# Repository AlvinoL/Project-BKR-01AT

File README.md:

# Project-BKR-01AT
Prova final de circuitos impressos

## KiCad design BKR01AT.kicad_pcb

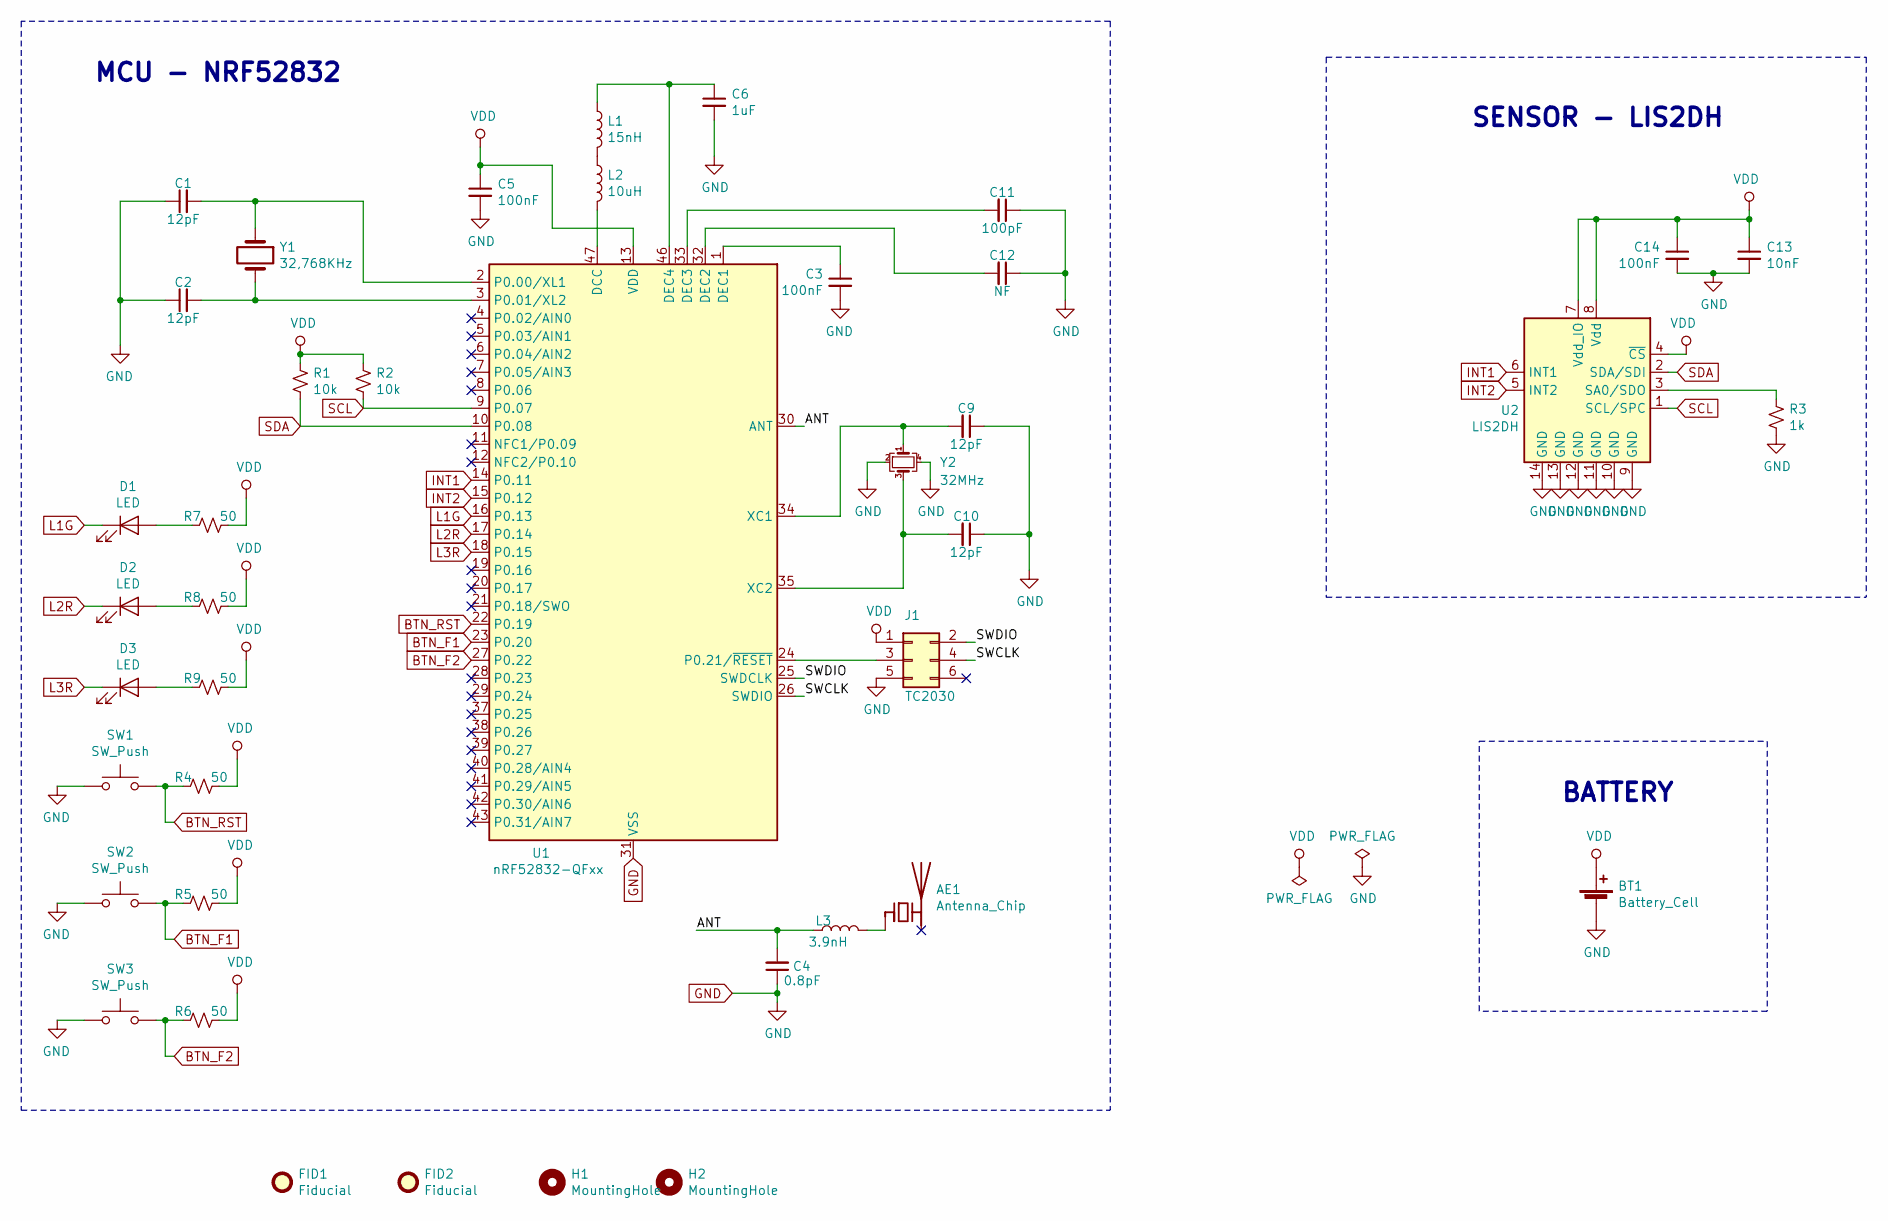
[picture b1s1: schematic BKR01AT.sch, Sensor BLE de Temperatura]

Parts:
AE1: Antenna_Chip; 2450AT18B100
BT1: Battery_Cell; Battery_Panasonic_CR2032-VS1N_Vertical_CircularHoles
C1, C2, C9, C10: 12pF; C_0402_1005Metric
C3, C5, C14: 100nF; C_0402_1005Metric
C4: 0.8pF; C_0402_1005Metric
C6: 1uF; C_0402_1005Metric
C11: 100pF; C_0402_1005Metric
C12: NF; C_0402_1005Metric
C13: 10nF; C_0402_1005Metric
D1, D2, D3: LED; LED_0402_1005Metric
FID1, FID2: Fiducial; Fiducial_0.5mm_Mask1.5mm
H1, H2: MountingHole; MountingHole_2mm
J1: TC2030; Tag-Connect_TC2030-IDC-NL_2x03_P1.27mm_Vertical
L1: 15nH; L_0402_1005Metric
L2: 10uH; L_0805_2012Metric
L3: 3.9nH; L_0402_1005Metric
R1, R2: 10k; R_0402_1005Metric
R3: 1k; R_0402_1005Metric
R4, R5, R6, R7, R8, R9: 50; R_0402_1005Metric
SW1, SW2, SW3: SW_Push; SW_Push_1P1T_NO_6x6mm_H9.5mm
U1: nRF52832-QFxx; QFN-48-1EP_6x6mm_P0.4mm_EP4.6x4.6mm
U2: LIS2DH; LGA-14_2x2mm_P0.35mm_LayoutBorder3x4y
Y1: 32,768KHz; Crystal_SMD_3215-2Pin_3.2x1.5mm
Y2: 32MHz; Crystal_SMD_2016-4Pin_2.0x1.6mm

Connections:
/ANT: C4.2, L3.1, U1.30 (ANT)
/SWCLK: J1.4, U1.26 (SWDIO)
/SWDIO: J1.2, U1.25 (SWDCLK)
BTN_F1: R5.2, SW2.2, U1.23 (P0.20)
BTN_F2: R6.2, SW3.2, U1.27 (P0.22)
BTN_RST: R4.2, SW1.2, U1.22 (P0.19)
GND: BT1.2 (-), C1.1, C2.1, C3.2, C4.1, C5.2, C6.2, C9.1, C10.1, C11.1, C12.1, C13.2, C14.2, J1.5, R3.2, SW1.1, SW2.1, SW3.1, U1.31 (VSS), U1.45 (VSS), U1.49 (VSS), U2.9 (GND), U2.10 (GND), U2.11 (GND), U2.12 (GND), U2.13 (GND), U2.14 (GND), Y2.2, Y2.4
INT1: U1.14 (P0.11), U2.6 (INT1)
INT2: U1.15 (P0.12), U2.5 (INT2)
L1G: D1.1 (K), U1.16 (P0.13)
L2R: D2.1 (K), U1.17 (P0.14)
L3R: D3.1 (K), U1.18 (P0.15)
unnamed: AE1.1 (FEED), L3.2
unnamed: C1.2, U1.2 (P0.00/XL1), Y1.1
unnamed: C2.2, U1.3 (P0.01/XL2), Y1.2
unnamed: C3.1, U1.1 (DEC1)
unnamed: C6.1, L1.1, U1.46 (DEC4)
unnamed: C9.2, U1.34 (XC1), Y2.1
unnamed: C10.2, U1.35 (XC2), Y2.3
unnamed: C11.2, U1.33 (DEC3)
unnamed: C12.2, U1.32 (DEC2)
unnamed: D1.2 (A), R7.2
unnamed: D2.2 (A), R8.2
unnamed: D3.2 (A), R9.2
unnamed: J1.3, U1.24 (P0.21/~RESET)
unnamed: L1.2, L2.1
unnamed: L2.2, U1.47 (DCC)
unnamed: R3.1, U2.3 (SA0/SDO)
SCL: R2.2, U1.9 (P0.07), U2.1 (SCL/SPC)
SDA: R1.2, U1.10 (P0.08), U2.2 (SDA/SDI)
VDD: BT1.1 (+), C5.1, C13.1, C14.1, J1.1, R1.1, R2.1, R4.1, R5.1, R6.1, R7.1, R8.1, R9.1, U1.13 (VDD), U1.36 (VDD), U1.48 (VDD), U2.4 (~CS), U2.7 (Vdd_IO), U2.8 (Vdd)

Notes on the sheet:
SENSOR - LIS2DH
BATTERY
MCU - NRF52832

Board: 2 copper layers, 41 parts (0 on the bottom side), 31 nets, no tracks yet.

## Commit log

2020-03-03 sch-project
